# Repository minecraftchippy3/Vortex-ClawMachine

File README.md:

# Vortex-ClawMachine
****

Vortex is a working small claw machine powered by an esp32. Built for Hack Club Fallen 2026

It is intended to be used as a fun tiny claw machine that can fit on a desk. It uses a large glowing button, along with a fun arcade joystick to control a claw that can pick up small prizes.

# Features & Design

The Claw Machine uses an XY gantry design using 2 lead ball screws, inspired by 3D printers. The claw machine also includes a small prize chute that can handle prizes up to 6 cm wide. I first had this idea for a project a while ago, when I saw how cool the gantry design was in a claw machine at an arcade. I had the idea for a while until an event called HackClub Fallen occurred. I decided this would be the perfect opportunity to create the claw machine I wanted to build. 

This small claw machine that can fit on your desk uses a wall power supply and uses stepper motors to control the main claw carriage. It also has a claw with 3 grabbers, which are all controlled by one linear actuator. 2 Nema stepper motors control the Gantry system, while the claw lowering mechanism is controlled by a regular DC motor.
# PCB & Components
For each Motor and Linear Actuator, I have a different designated motor driver. Each motor driver also uses a decoupling capacitator, and I am using a step down converter to change the voltage from the wall power source to a suitable 5 volts for controlling the esp32. It uses two rows of pin headers to allow for each component to get plugged in easily. The PCB design fits all of this into a small board that allows for easy connections to the components. A full list of all components is provided in the tutorial section.

# Firmware

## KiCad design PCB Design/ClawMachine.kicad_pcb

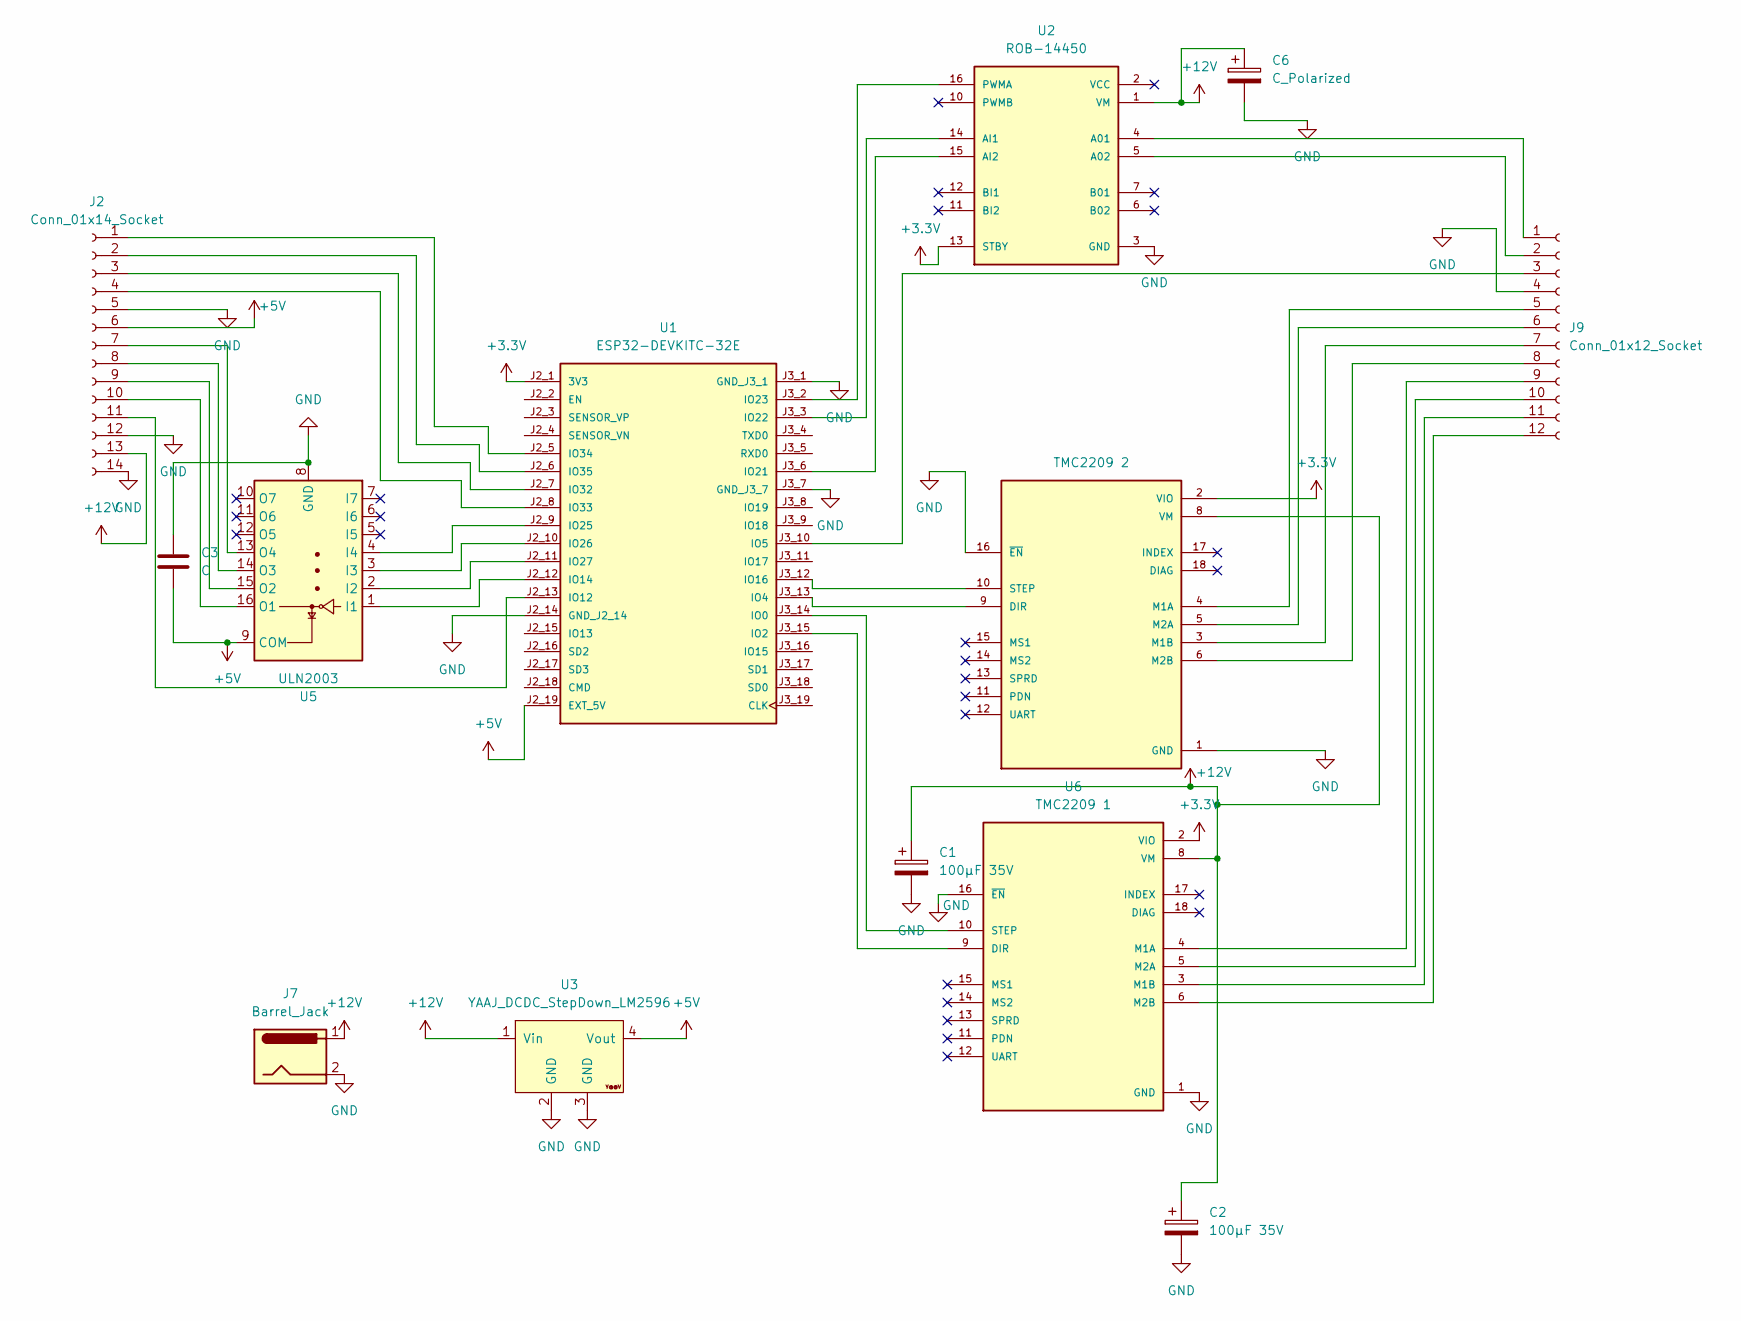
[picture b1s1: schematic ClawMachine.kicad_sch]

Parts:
C1, C2: 100µF 35V; CP_Radial_D8.0mm_P3.50mm
C3: C; C_Rect_L4.0mm_W2.5mm_P2.50mm
C6: C_Polarized; CP_Radial_D8.0mm_P3.50mm
J2: Conn_01x14_Socket; PinSocket_1x14_P2.54mm_Vertical
J7: Barrel_Jack; BarrelJack_CUI_PJ-063AH_Horizontal
J9: Conn_01x12_Socket; PinSocket_1x12_P2.54mm_Vertical
U1: ESP32-DEVKITC-32E; MODULE_ESP32-DEVKITC-32E; PARTREV 1.4
U2: ROB-14450; YOO, ITS THE 67 KID; MPN ROB-14450
U3: YAAJ_DCDC_StepDown_LM2596
U4: TMC2209 2; MODULE_TMC2209_SILENTSTEPSTICK; PARTREV 1.20
U5: ULN2003; DIP-16_W7.62mm
U6: TMC2209 1; MODULE_TMC2209_SILENTSTEPSTICK; PARTREV 1.20

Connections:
+3.3V: U1.J2_1 (3V3), U2.13 (STBY), U4.2 (VIO), U6.2 (VIO)
+5V: C3.2, J2.6, U1.J2_19 (EXT_5V), U3.4 (Vout), U5.9 (COM)
+12V: C1.1, C2.1, C6.1, J2.13, J7.1, U2.1 (VM), U3.1 (Vin), U4.8 (VM), U6.8 (VM)
GND: C1.2, C2.2, C3.1, C6.2, J2.5, J2.12, J2.14, J7.2, J9.4, U1.J2_14 (GND_J2_14), U1.J3_1 (GND_J3_1), U1.J3_7 (GND_J3_7), U2.3 (GND), U2.8 (GND), U2.9 (GND), U3.2 (GND), U3.3 (GND), U4.1 (GND), U4.7 (GND), U4.16 (~EN), U5.8 (GND), U6.1 (GND), U6.7 (GND), U6.16 (~EN)
unnamed: J2.1, U1.J2_5 (IO34)
unnamed: J2.2, U1.J2_6 (IO35)
unnamed: J2.3, U1.J2_7 (IO32)
unnamed: J2.4, U1.J2_8 (IO33)
unnamed: J2.7, U5.13 (O4)
unnamed: J2.8, U5.14 (O3)
unnamed: J2.9, U5.15 (O2)
unnamed: J2.10, U5.16 (O1)
unnamed: J2.11, U1.J2_13 (IO12)
unnamed: J9.1, U2.4 (A01)
unnamed: J9.2, U2.5 (A02)
unnamed: J9.3, U1.J3_10 (IO5)
unnamed: J9.5, U4.4 (M1A)
unnamed: J9.6, U4.5 (M2A)
unnamed: J9.7, U4.3 (M1B)
unnamed: J9.8, U4.6 (M2B)
unnamed: J9.9, U6.4 (M1A)
unnamed: J9.10, U6.5 (M2A)
unnamed: J9.11, U6.3 (M1B)
unnamed: J9.12, U6.6 (M2B)
unnamed: U1.J3_14 (IO0), U6.10 (STEP)
unnamed: U1.J3_15 (IO2), U6.9 (DIR)
unnamed: U1.J3_13 (IO4), U4.9 (DIR)
unnamed: U1.J2_12 (IO14), U5.1 (I1)
unnamed: U1.J3_12 (IO16), U4.10 (STEP)
unnamed: U1.J3_6 (IO21), U2.15 (AI2)
unnamed: U1.J3_3 (IO22), U2.14 (AI1)
unnamed: U1.J3_2 (IO23), U2.16 (PWMA)
unnamed: U1.J2_9 (IO25), U5.4 (I4)
unnamed: U1.J2_10 (IO26), U5.3 (I3)
unnamed: U1.J2_11 (IO27), U5.2 (I2)

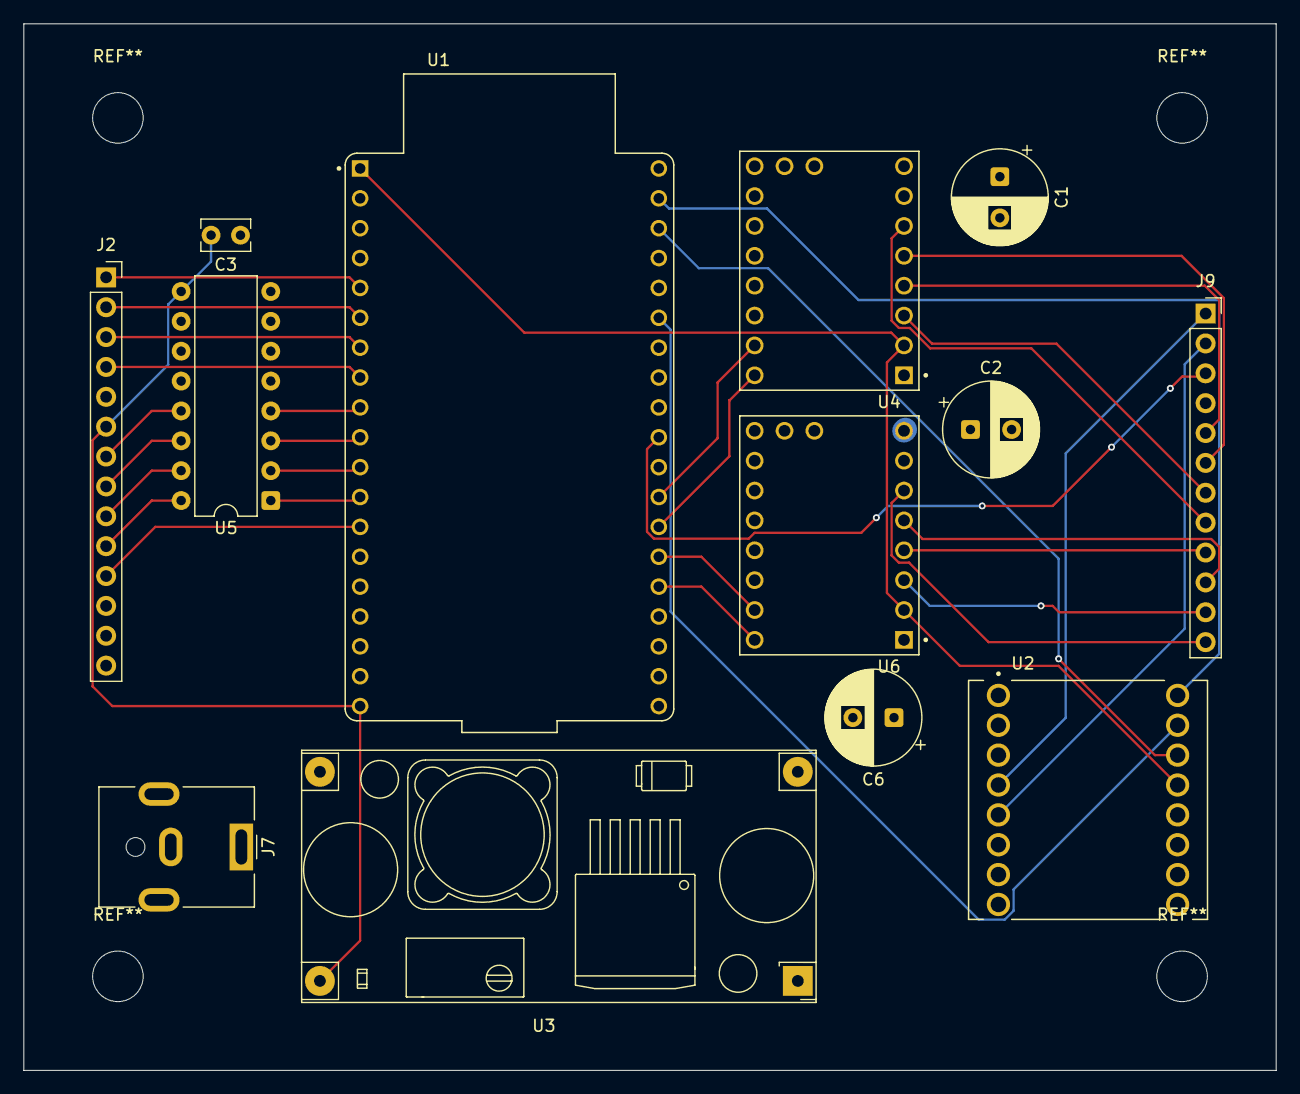
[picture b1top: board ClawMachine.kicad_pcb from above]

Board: 4 copper layers, 106.5 x 89.0 mm, 13 parts (0 on the bottom side), 35 nets.
